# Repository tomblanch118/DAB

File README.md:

# DAB
Electronics schematics, mechanical design and code for the Defuse a Bomb team building activity.

## PCB Version 1.0
There are a few issues with the first version of the PCB, I used A7 and A6 for controlling the RGB LEDs and as the spare io pin. I missed the fact that these pins are analog inputs only (straight to the analog mux). As such version 1 of the pcb requires a few bodge wires from the icsp pins to the leds and buzzer to make it work. As the icsp pins are only used once to burn the bootloader this isnt really a problem and version 2 of the board will fix this. 

You can power the board from an ftdi cable/board however this results in backpowering the 5v regulator/no power to the 3.3v regulator. So far this hasnt proved to be a problem but it probably isnt ideal, YMMV. In future the 5v from the usb bus could be connected to vin but there is a good chance that the 5v regulators dropout voltage will mean that this wont work.

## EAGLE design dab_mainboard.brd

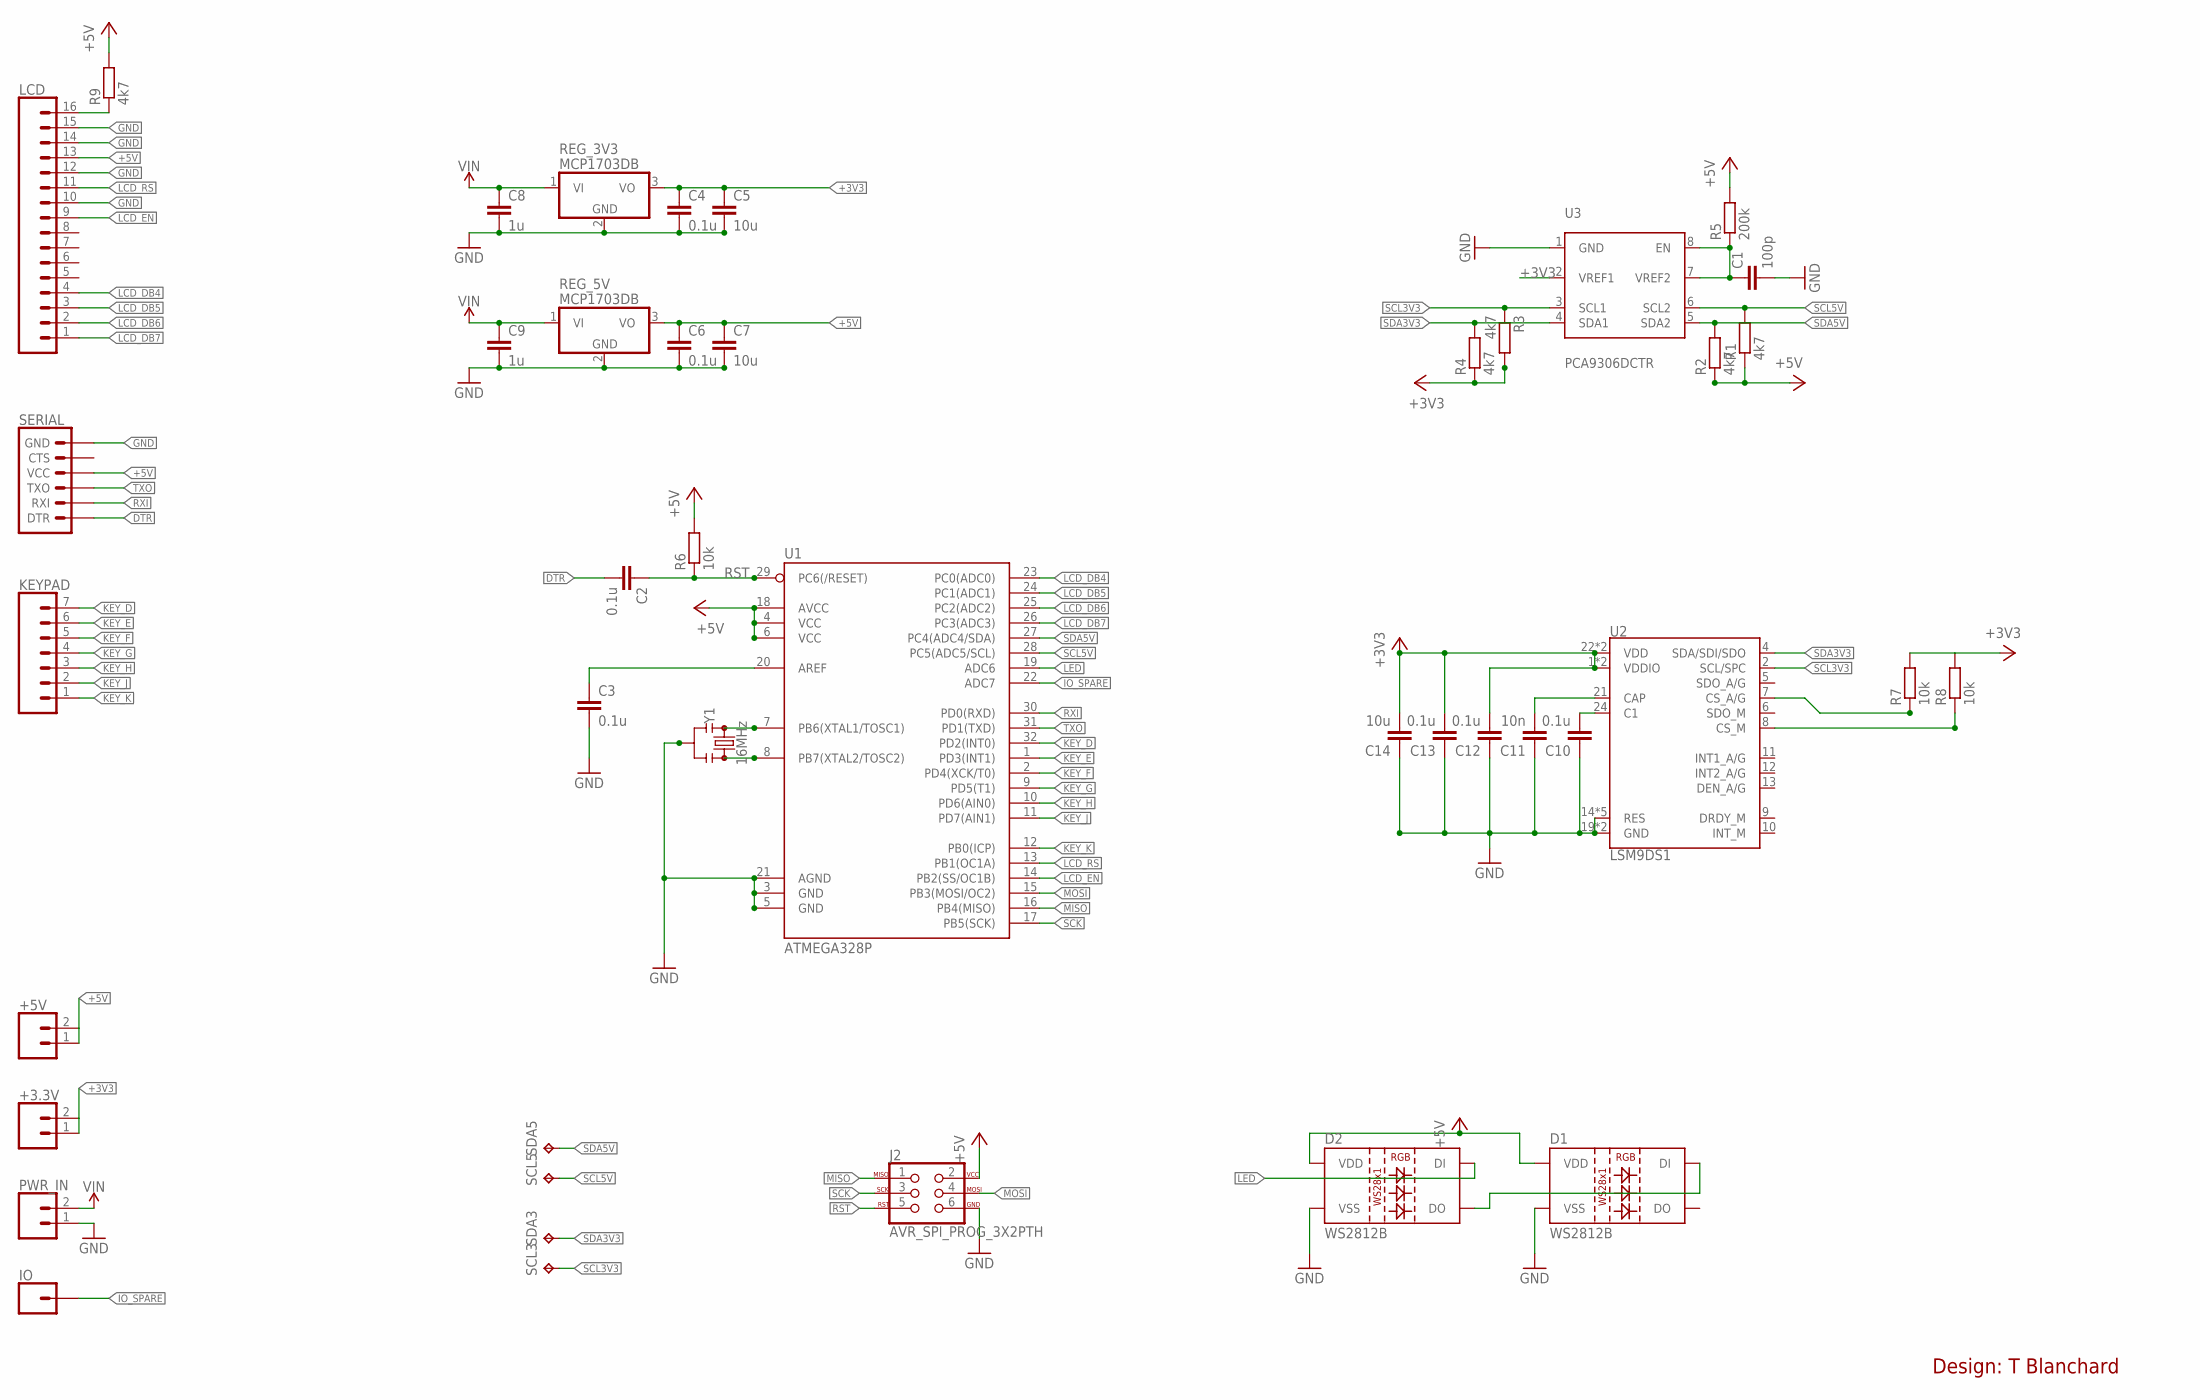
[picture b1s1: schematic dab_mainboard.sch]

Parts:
+3.3V, +5V: CONN_02; 1X02
C1: 100p; C0603
C2, C3, C4, C6, C10, C12, C13: 0.1u; C0603
C5, C7, C14: 10u; C0603
C8, C9: 1u; C0603
C11: 10n; C0603
D1, D2: WS2812B
IO: CONN_01; 1X01
J2: AVR_SPI_PROG_3X2PTH; 2X3
KEYPAD: CONN_07; 1X07
LCD: CONN_16; 1X16
PWR_IN: CONN_02; 1X02
R1, R2, R3, R4, R9: 4k7; R0603
R5: 200k; R0603
R6, R7, R8: 10k; R0603
REG_3V3, REG_5V: MCP1703DB; SOT223
SCL3, SCL5: TPTP08R; TP08R
SDA3, SDA5: TPTP08R; TP08R
SERIAL: 6_PIN_SERIAL_TARGETSILK; 6_PIN_SERIAL_TARGET_SIDE_W_SILK
U1: ATMEGA328P; TQFP32-08
U2: LSM9DS1; LGA-24-3.5X3
U3: PCA9306DCTR; SM8
Y1: 16MHz; RESONATOR-SMD-3.2X1.3

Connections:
+3V3: +3.3V.1, +3.3V.2, C4.1, C5.1, C12.2, C13.2, C14.2, R3.2, R4.1, R7.2, R8.2, REG_3V3.3 (VO), U2.1 (VDDIO), U2.3 (VDDIO), U2.22 (VDD), U2.23 (VDD), U3.2 (VREF1)
+5V: +5V.1, +5V.2, C6.1, C7.1, D1.1 (VDD), D2.1 (VDD), J2.2, LCD.13, R1.1, R2.1, R5.2, R6.2, R9.2, REG_5V.3 (VO), SERIAL.P$4 (VCC), U1.4 (VCC), U1.6 (VCC), U1.18 (AVCC)
CS_A/G: R7.1, U2.7 (CS_A/G)
CS_M: R8.1, U2.8 (CS_M)
DTR: C2.2, SERIAL.P$1 (DTR)
GND: C1.2, C3.2, C4.2, C5.2, C6.2, C7.2, C8.2, C9.2, C10.1, C11.1, C12.1, C13.1, C14.1, D1.3 (VSS), D2.3 (VSS), J2.6, LCD.10, LCD.12, LCD.14, LCD.15, PWR_IN.1, REG_3V3.2 (GND), REG_5V.2 (GND), SERIAL.P$6 (GND), U1.3 (GND), U1.5 (GND), U1.21 (AGND), U2.14 (RES), U2.15 (RES), U2.16 (RES), U2.17 (RES), U2.18 (RES), U2.19 (GND), U2.20 (GND), U3.1 (GND), Y1.2
IO_SPARE: IO.1, U1.22 (ADC7)
KEY_D: KEYPAD.7, U1.32 (PD2(INT0))
KEY_E: KEYPAD.6, U1.1 (PD3(INT1))
KEY_F: KEYPAD.5, U1.2 (PD4(XCK/T0))
KEY_G: KEYPAD.4, U1.9 (PD5(T1))
KEY_H: KEYPAD.3, U1.10 (PD6(AIN0))
KEY_J: KEYPAD.2, U1.11 (PD7(AIN1))
KEY_K: KEYPAD.1, U1.12 (PB0(ICP))
LCD_DB4: LCD.4, U1.23 (PC0(ADC0))
LCD_DB5: LCD.3, U1.24 (PC1(ADC1))
LCD_DB6: LCD.2, U1.25 (PC2(ADC2))
LCD_DB7: LCD.1, U1.26 (PC3(ADC3))
LCD_EN: LCD.9, U1.14 (PB2(SS/OC1B))
LCD_RS: LCD.11, U1.13 (PB1(OC1A))
LED: D2.4 (DI), U1.19 (ADC6)
MISO: J2.1, U1.16 (PB4(MISO))
MOSI: J2.4, U1.15 (PB3(MOSI/OC2))
unnamed: C1.1, R5.1, U3.7 (VREF2), U3.8 (EN)
unnamed: U1.7 (PB6(XTAL1/TOSC1)), Y1.1
unnamed: U1.8 (PB7(XTAL2/TOSC2)), Y1.3
unnamed: C3.1, U1.20 (AREF)
unnamed: LCD.16, R9.1
unnamed: C10.2, U2.24 (C1)
unnamed: C11.2, U2.21 (CAP)
unnamed: D1.4 (DI), D2.2 (DO)
RST: C2.1, J2.5, R6.1, U1.29 (PC6(/RESET))
RXI: SERIAL.P$3 (RXI), U1.30 (PD0(RXD))
SCK: J2.3, U1.17 (PB5(SCK))
SCL3V3: R3.1, SCL3.TP, U2.2 (SCL/SPC), U3.3 (SCL1)
SCL5V: R1.2, SCL5.TP, U1.28 (PC5(ADC5/SCL)), U3.6 (SCL2)
SDA3V3: R4.2, SDA3.TP, U2.4 (SDA/SDI/SDO), U3.4 (SDA1)
SDA5V: R2.2, SDA5.TP, U1.27 (PC4(ADC4/SDA)), U3.5 (SDA2)
TXO: SERIAL.P$2 (TXO), U1.31 (PD1(TXD))
VIN: C8.1, C9.1, PWR_IN.2, REG_3V3.1 (VI), REG_5V.1 (VI)

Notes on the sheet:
Design: T Blanchard

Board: 2 copper layers, 43 parts (0 on the bottom side), 40 nets, no tracks yet.

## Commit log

2017-07-06 :octocat: Added .gitattributes & .gitignore files
2017-07-06 Defuse A Bomb Game
    Code and pcb/schematics for the Defuse A Bomb Gregynog Game.
2017-07-25 Version 1 Final
2017-10-13 Added V1 Code
    Working version of the code. Uses keypad,lcd, buzzer, accelerometer and
    leds.
2017-10-22 Added 2d design files
    Moved eagle pcb files and added 2d designs suitable for laser cutting.
2018-10-09 Settings change
    Changed one of the motion sensor disable buttons from # to 7 so that it doesn't clash with the resetting the bomb .

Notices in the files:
parts and their libraries:
SparkFun-LED: Licensing: Creative Commons ShareAlike 4.0 International - https://creativecommons.org/licenses/by-sa/4.0
